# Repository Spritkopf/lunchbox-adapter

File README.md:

# Introduction

This is my interpretation of the *BrotboxErsatzPlatine* instrument adapter for the BMW K100. It is based on the circuit originally created by Maru (maru-labs.com).
Its purpose is to replace the original instrument unit of the BMW K100 (affectionately called *lunchbox* because of its distinctive shape) with 3rd party speedometer units. For more information have a look at maru-labs.com.
I extended the circuit according to my own needs and put together my own circuit board.

This project consists of the KiCAD design files for the schematic and PCB

# Features

* Plugs into the stock connector for the K100 instrument unit
* Convert signal of the original speed sensors to a square wave signal understood by most 3rd party speedos
* Conditioning of primary ignition coil RPM signal and conversion to square wave signal understood by most 3rd party speedos
* Provide excitation current for alternator
* Combine several of the information/warning lights to a common warning light output
* supports gear indicator (one wire for every gear)

## Speed signal voltage

The output voltage of the speed signal can be selected between 12V and a custom supply voltage at PIN1 (VCC) on the Gauges Connector (J5) by setting the jumper JP3 to the appropriate position

## RPM signal waveform

Depending on the type of tacho unit, the output waveform of the RPM signal can be selected between 12V Square wave (pulses to ground) and a sort of cleaned up raw ignition signal by setting jumper JP2 to the appropriate position. The square wave signal should be standard, the latter option is just there as an experiment.

## Warning lights

The warning lights for temperature (TMP), oil pressure (OIL), choke (CHK) and Light-test (LGHT) are displayed by individual LEDs on the board. Additionally, any number of them can be grouped together to a general warning lamp (WRN) if your dashboard has no space for this many lamps. Each of the 4 rows of Jumper JP1 can be bridged to select this warning signal to the general warning lamp. Please be aware that if only the general warning lamp is used you have no information on the source of the warning other than looking at the smd LEDs on the board.

# Credits

Thanks to maru (maru-labs.com) for the general idea. I re-used a lot of the circuit of the original BEP.
Thanks to user `robmack` from k100-forum.com from whom I stole the RPM conditioning circuit.

# No warranty

I created this as a hobby project as an experiment / exercise. I will not be responsible for any damage caused to your bike by using all of or parts of this circuit. Use at your own risk.

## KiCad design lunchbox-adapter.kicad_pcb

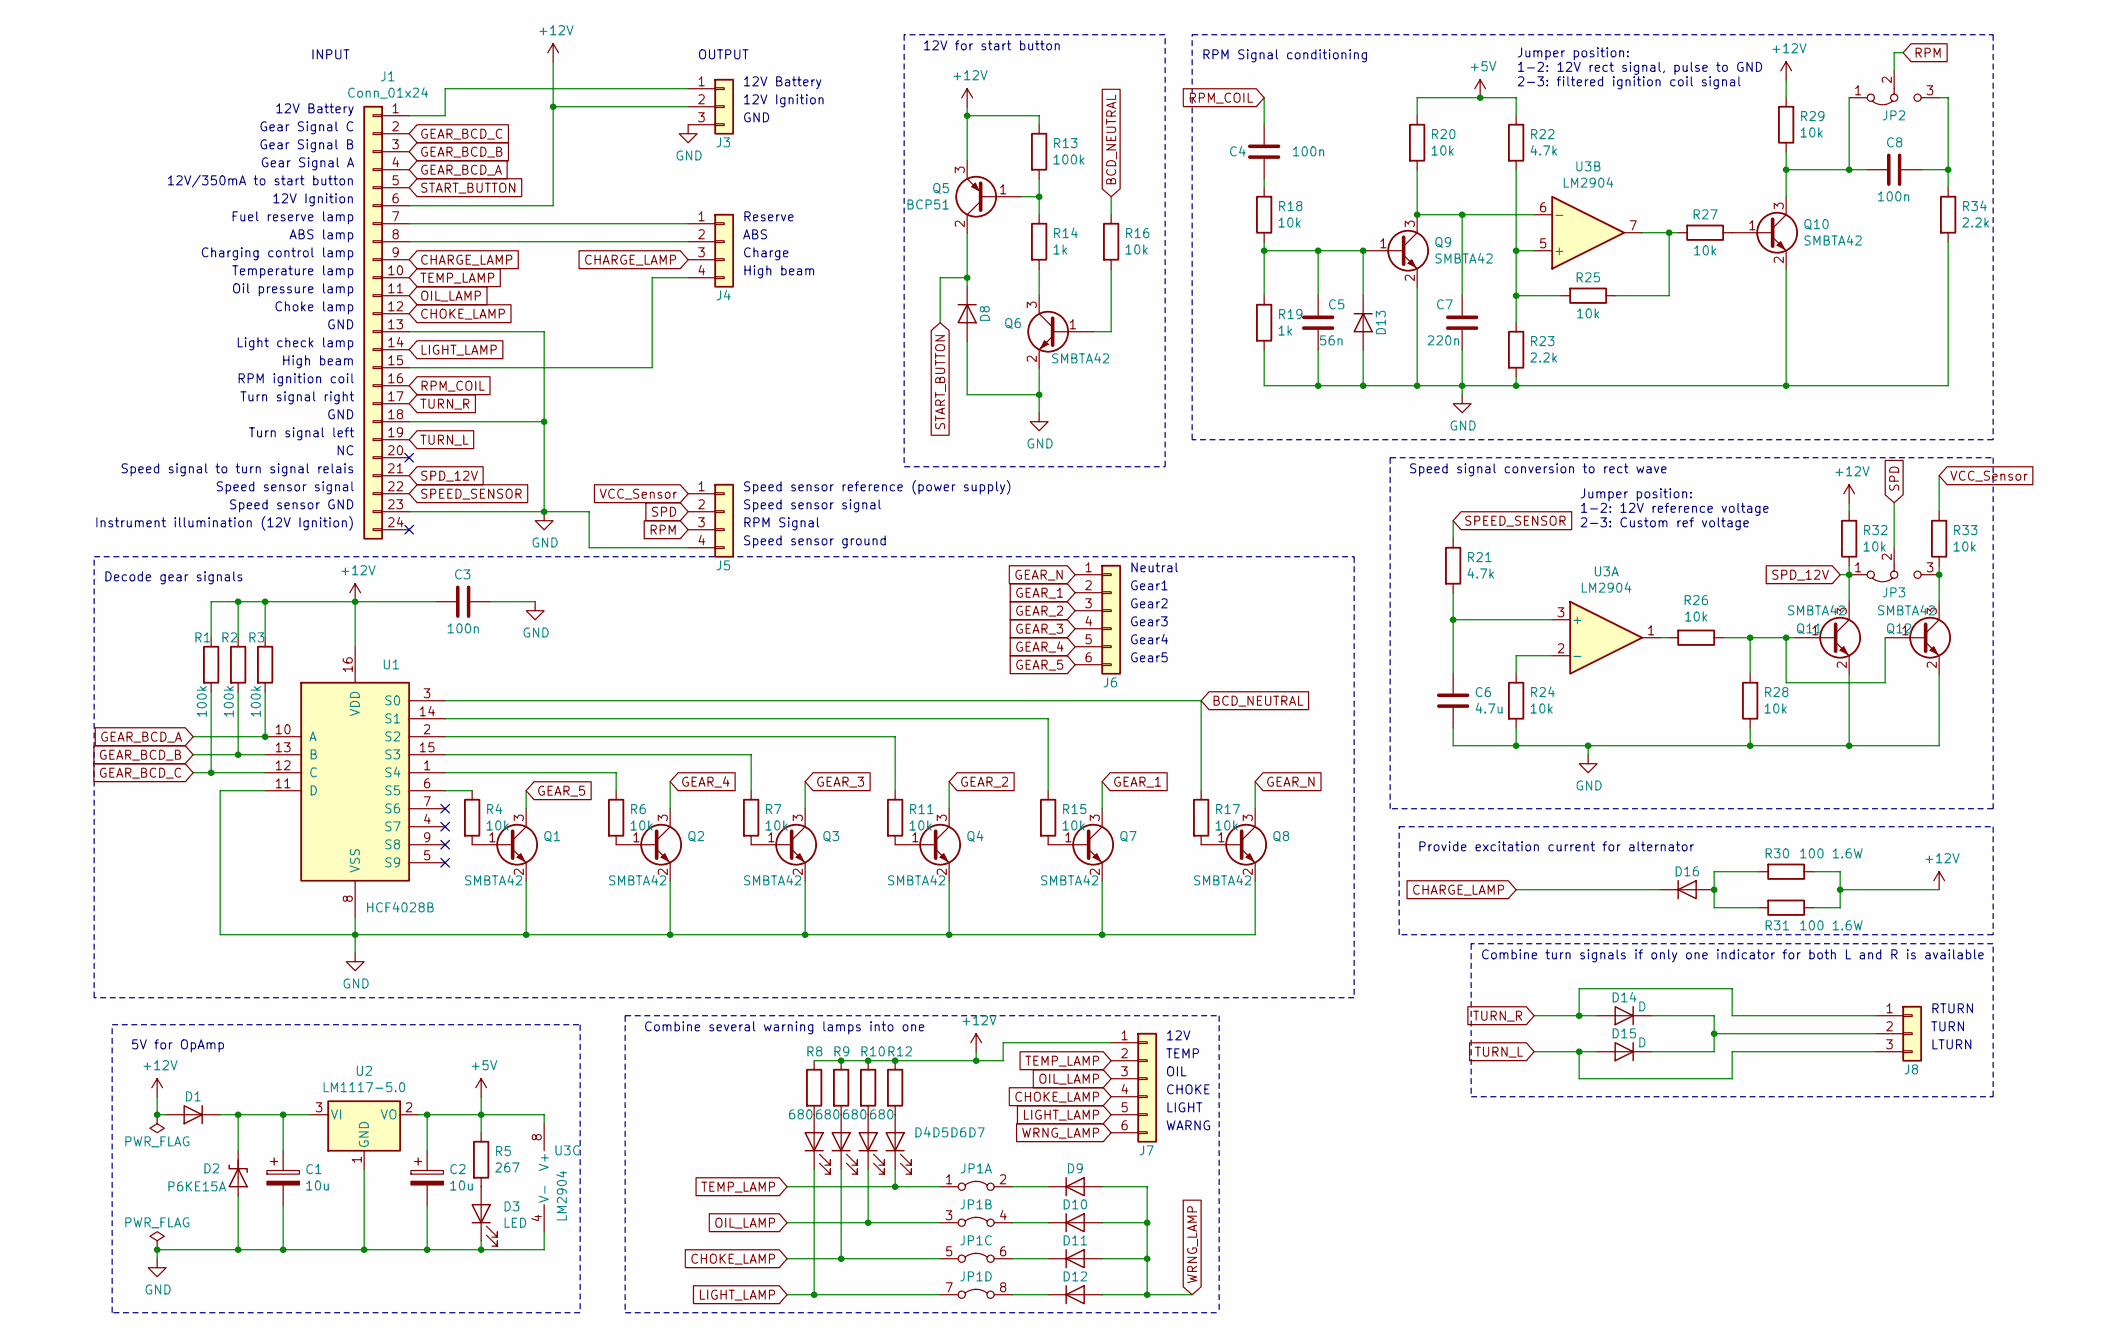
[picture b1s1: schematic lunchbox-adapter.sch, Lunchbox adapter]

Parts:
C1, C2: 10u; CP_Elec_4x5.8
C3, C4, C8: 100n; C_1206_3216Metric_Pad1.42x1.75mm_HandSolder
C5: 56n; C_0603_1608Metric_Pad1.05x0.95mm_HandSolder
C6: 4.7u; C_1206_3216Metric_Pad1.42x1.75mm_HandSolder
C7: 220n; C_1206_3216Metric_Pad1.42x1.75mm_HandSolder
D1, D8, D9, D10, D11, D12, D13, D14, D15, D16: D; D_0603_1608Metric_Pad1.05x0.95mm_HandSolder
D2: P6KE15A; D_DO-15_P12.70mm_Horizontal
D3, D4, D5, D6, D7: LED; LED_1206_3216Metric_Pad1.42x1.75mm_HandSolder
J1: Conn_01x24; DIP-24_866
J3, J8: Conn_01x03; PinHeader_1x03_P2.54mm_Vertical
J4, J5: Conn_01x03; PinHeader_1x04_P2.54mm_Vertical
J6, J7: Conn_01x06; PinHeader_1x06_P2.54mm_Vertical
JP1: Jumper_4x2; PinHeader_2x04_P2.54mm_Vertical
JP2, JP3: Jumper_3_Bridged12; PinHeader_1x03_P2.54mm_Vertical
Q1, Q2, Q3, Q4, Q6, Q7, Q8, Q9, Q10, Q11, Q12: SMBTA42; SOT-23
Q5: BCP51; SOT-223
R1, R2, R3, R13: 100k; R_1206_3216Metric_Pad1.42x1.75mm_HandSolder
R4, R6, R7, R11, R15, R16, R17, R18, R20, R24, R25, R26, R27, R28, R29, R32, R33: 10k; R_0805_2012Metric_Pad1.15x1.40mm_HandSolder
R5: 267; R_1206_3216Metric_Pad1.42x1.75mm_HandSolder
R8, R9, R10, R12: 680; R_0805_2012Metric_Pad1.15x1.40mm_HandSolder
R14, R19: 1k; R_0805_2012Metric_Pad1.15x1.40mm_HandSolder
R21, R22: 4.7k; R_0805_2012Metric_Pad1.15x1.40mm_HandSolder
R23, R34: 2.2k; R_0805_2012Metric_Pad1.15x1.40mm_HandSolder
R30, R31: 100 1.6W; 5020_resistor_thermal_pads
U1: HCF4028B; SOIC-16_3.9x9.9mm_P1.27mm
U2: LM1117-5.0; SOT-223-3_TabPin2
U3: LM2904; SO-8_3.9x4.9mm_P1.27mm

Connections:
+5V: C2.1, R5.1, R20.1, R22.1, U2.2 (VO), U3.8 (V+)
+12V: C3.1, D1.2 (A), J1.6, J3.2, J7.1, Q5.3 (E), R1.1, R2.1, R3.1, R8.1, R9.1, R10.1, R12.1, R13.1, R29.2, R30.1, R31.1, R32.2, U1.16 (VDD)
BCD_NEUTRAL: R16.1, R17.1, U1.3 (S0)
CHARGE_LAMP: D16.1 (K), J1.9, J4.3
CHOKE_LAMP: D5.1 (K), J1.12, J7.4, JP1.5
GEAR_1: J6.2, Q7.3 (C)
GEAR_2: J6.3, Q4.3 (C)
GEAR_3: J6.4, Q3.3 (C)
GEAR_4: J6.5, Q2.3 (C)
GEAR_5: J6.6, Q1.3 (C)
GEAR_BCD_A: J1.4, R3.2, U1.10 (A)
GEAR_BCD_B: J1.3, R2.2, U1.13 (B)
GEAR_BCD_C: J1.2, R1.2, U1.12 (C)
GEAR_N: J6.1, Q8.3 (C)
GND: C1.2, C2.2, C3.2, C5.2, C6.2, C7.2, D2.2 (A2), D3.1 (K), D8.2 (A), D13.2 (A), J1.13, J1.18, J1.23, J3.3, J5.4, Q1.2 (E), Q2.2 (E), Q3.2 (E), Q4.2 (E), Q6.2 (E), Q7.2 (E), Q8.2 (E), Q9.2 (E), Q10.2 (E), Q11.2 (E), Q12.2 (E), R19.2, R23.2, R24.2, R28.1, R34.2, U1.8 (VSS), U1.11 (D), U2.1 (GND), U3.4 (V-)
LIGHT_LAMP: D4.1 (K), J1.14, J7.5, JP1.7
unnamed: C1.1, D1.1 (K), D2.1 (A1), U2.3 (VI)
unnamed: C4.2, R18.2
unnamed: C5.1, D13.1 (K), Q9.1 (B), R18.1, R19.1
unnamed: C6.1, R21.2, U3.3 (+)
unnamed: C7.1, Q9.3 (C), R20.2, U3.6 (-)
unnamed: C8.1, JP2.3 (B), R34.1
unnamed: C8.2, JP2.1 (A), Q10.3 (C), R29.1
unnamed: D3.2 (A), R5.2
unnamed: D4.2 (A), R8.2
unnamed: D5.2 (A), R9.2
unnamed: D6.2 (A), R10.2
unnamed: D7.2 (A), R12.2
unnamed: D9.1 (K), JP1.2
unnamed: D10.1 (K), JP1.4
unnamed: D11.1 (K), JP1.6
unnamed: D12.1 (K), JP1.8
unnamed: D14.1 (K), D15.1 (K), J8.2
unnamed: D16.2 (A), R30.2, R31.2
unnamed: J1.1, J3.1
unnamed: J1.7, J4.1
unnamed: J1.8, J4.2
unnamed: J1.15, J4.4
unnamed: JP3.3 (B), Q12.3 (C), R33.1
unnamed: Q1.1 (B), R4.2
unnamed: Q2.1 (B), R6.2
unnamed: Q3.1 (B), R7.2
unnamed: Q4.1 (B), R11.2
unnamed: Q5.1 (B), R13.2, R14.1
unnamed: Q6.1 (B), R16.2
unnamed: Q6.3 (C), R14.2
unnamed: Q7.1 (B), R15.2
unnamed: Q8.1 (B), R17.2
unnamed: Q10.1 (B), R27.1
unnamed: Q11.1 (B), Q12.1 (B), R26.1, R28.2
unnamed: R4.1, U1.6 (S5)
unnamed: R6.1, U1.1 (S4)
unnamed: R7.1, U1.15 (S3)
unnamed: R11.1, U1.2 (S2)
unnamed: R15.1, U1.14 (S1)
unnamed: R22.2, R23.1, R25.2, U3.5 (+)
unnamed: R24.1, U3.2 (-)
unnamed: R25.1, R27.2, U3.7
unnamed: R26.2, U3.1
OIL_LAMP: D6.1 (K), J1.11, J7.3, JP1.3
RPM: J5.3, JP2.2 (C)
RPM_COIL: C4.1, J1.16
SPD: J5.2, JP3.2 (C)
SPD_12V: J1.21, JP3.1 (A), Q11.3 (C), R32.1
SPEED_SENSOR: J1.22, R21.1
START_BUTTON: D8.1 (K), J1.5, Q5.2 (C)
TEMP_LAMP: D7.1 (K), J1.10, J7.2, JP1.1
TURN_L: D15.2 (A), J1.19, J8.3
TURN_R: D14.2 (A), J1.17, J8.1
VCC_Sensor: J5.1, R33.2
WRNG_LAMP: D9.2 (A), D10.2 (A), D11.2 (A), D12.2 (A), J7.6

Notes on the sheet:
12V Battery
Gear Signal C
Gear Signal B
Gear Signal A
12V/350mA to start button
12V Ignition
Fuel reserve lamp
ABS lamp
Charging control lamp
Temperature lamp
Oil pressure lamp
Choke lamp
GND
Light check lamp
High beam
RPM ignition coil
Turn signal right
Turn signal left
Speed signal to turn signal relais
Speed sensor signal
Speed sensor GND
Instrument illumination (12V Ignition)
Speed signal conversion to rect wave
INPUT
OUTPUT
Combine turn signals if only one indicator for both L and R is available
Combine several warning lamps into one
12V for start button
Provide excitation current for alternator
Decode gear signals
5V for OpAmp
RPM Signal conditioning
Jumper position: 1-2: 12V rect signal, pulse to GND 2-3: filtered ignition coil signal
Gear1
Gear2
Gear3
Gear4
Gear5
Neutral
Speed sensor reference (power supply)

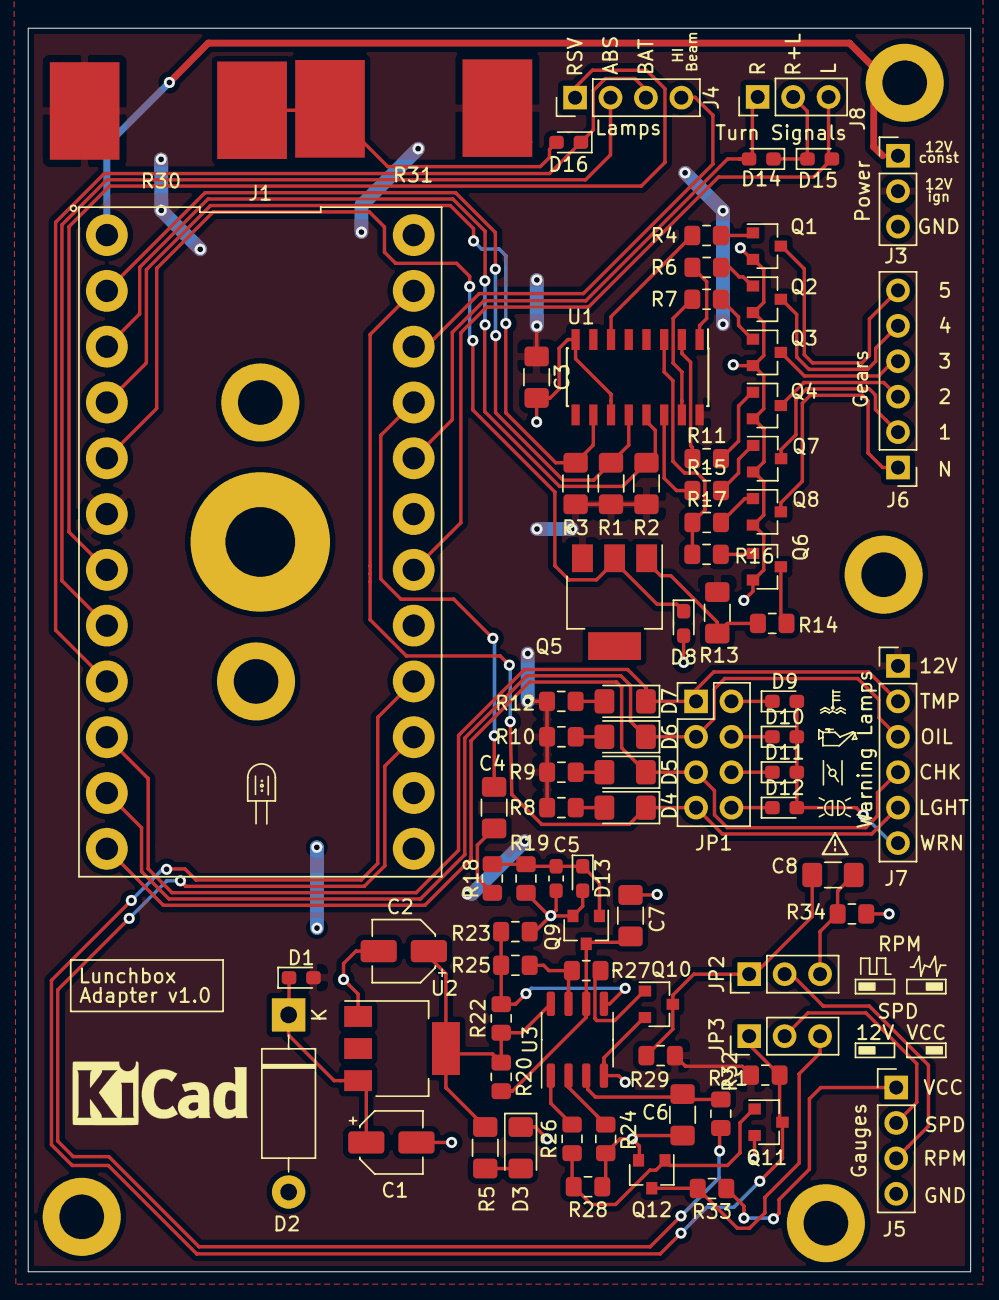
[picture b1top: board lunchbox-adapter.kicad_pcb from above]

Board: 2 copper layers, 67.6 x 89.2 mm, 83 parts (0 on the bottom side), 71 nets.

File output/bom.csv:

"Reference","Qty","Value","DNP","Exclude from BOM","Exclude from Board","Footprint","Datasheet"
"C1,C2","2","10u","","","","Capacitor_SMD:CP_Elec_4x5.8","~"
"C3,C4,C8","3","100n","","","","Capacitor_SMD:C_1206_3216Metric_Pad1.42x1.75mm_HandSolder","~"
"C5","1","56n","","","","Capacitor_SMD:C_0603_1608Metric_Pad1.05x0.95mm_HandSolder","~"
"C6","1","4.7u","","","","Capacitor_SMD:C_1206_3216Metric_Pad1.42x1.75mm_HandSolder","~"
"C7","1","220n","","","","Capacitor_SMD:C_1206_3216Metric_Pad1.42x1.75mm_HandSolder","~"
"D1,D8,D9,D10,D11,D12,D13,D14,D15,D16","10","D","","","","Diode_SMD:D_0603_1608Metric_Pad1.05x0.95mm_HandSolder","~"
"D2","1","P6KE15A","","","","Diode_THT:D_DO-15_P12.70mm_Horizontal","~"
"D3,D4,D5,D6,D7","5","LED","","","","LED_SMD:LED_1206_3216Metric_Pad1.42x1.75mm_HandSolder","~"
"J1","1","Conn_01x24","","","","bep:DIP-24_866","~"
"J3,J8","2","Conn_01x03","","","","Connector_PinHeader_2.54mm:PinHeader_1x03_P2.54mm_Vertical","~"
"J4,J5","2","Conn_01x03","","","","Connector_PinHeader_2.54mm:PinHeader_1x04_P2.54mm_Vertical","~"
"J6,J7","2","Conn_01x06","","","","Connector_PinHeader_2.54mm:PinHeader_1x06_P2.54mm_Vertical","~"
"JP1","1","Jumper_4x2","","","","Connector_PinHeader_2.54mm:PinHeader_2x04_P2.54mm_Vertical",""
"JP2,JP3","2","Jumper_3_Bridged12","","","","Connector_PinHeader_2.54mm:PinHeader_1x03_P2.54mm_Vertical","~"
"Q1,Q2,Q3,Q4,Q6,Q7,Q8,Q9,Q10,Q11,Q12","11","SMBTA42","","","","Package_TO_SOT_SMD:SOT-23","~"
"Q5","1","BCP51","","","","Package_TO_SOT_SMD:SOT-223","http://www.fairchildsemi.com/ds/BC/BCP51.pdf"
"R1,R2,R3,R13","4","100k","","","","Resistor_SMD:R_1206_3216Metric_Pad1.42x1.75mm_HandSolder","~"
"R4,R6,R7,R11,R15,R16,R17,R18,R20,R24,R25,R26,R27,R28,R29,R32,R33","17","10k","","","","Resistor_SMD:R_0805_2012Metric_Pad1.15x1.40mm_HandSolder","~"
"R5","1","267","","","","Resistor_SMD:R_1206_3216Metric_Pad1.42x1.75mm_HandSolder","~"
"R8,R9,R10,R12","4","680","","","","Resistor_SMD:R_0805_2012Metric_Pad1.15x1.40mm_HandSolder","~"
"R14,R19","2","1k","","","","Resistor_SMD:R_0805_2012Metric_Pad1.15x1.40mm_HandSolder","~"
"R21,R22","2","4.7k","","","","Resistor_SMD:R_0805_2012Metric_Pad1.15x1.40mm_HandSolder","~"
"R23,R34","2","2.2k","","","","Resistor_SMD:R_0805_2012Metric_Pad1.15x1.40mm_HandSolder","~"
"R30,R31","2","100 1.6W","","","","bep:5020_resistor_thermal_pads","~"
"U1","1","HCF4028B","","","","Package_SO:SOIC-16_3.9x9.9mm_P1.27mm","https://cdn-reichelt.de/documents/datenblatt/A240/MOS4028_SM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"
"U2","1","LM1117-5.0","","","","Package_TO_SOT_SMD:SOT-223-3_TabPin2","http://www.ti.com/lit/ds/symlink/lm1117.pdf"
"U3","1","LM2904","","","","Package_SO:SO-8_3.9x4.9mm_P1.27mm","http://www.ti.com/lit/ds/symlink/lm358.pdf"

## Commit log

2019-04-30 add empty kicad project
2019-05-02 add local symbol library, begin schematic
2019-05-03 first version of schematic finished
2019-05-03 add TSV diode to library
2019-05-03 finished logic of schematic
2019-05-06 finalized schematic
2019-05-10 output signals grouped to several connectors
2019-05-10 begin pcb
2019-05-16 finished pcb, review candidate
2019-05-16 cleanup repository
2019-05-16 renamed project
2019-05-17 finished pcb design
2019-05-17 add schematic PDF
2019-05-20 change power resitor footprints, cleanup
2019-05-21 cleanup mounting holes
2019-05-21 final; add gerber files for manufacturing
2025-12-15 add BOM and 3d printed housing CAD files
